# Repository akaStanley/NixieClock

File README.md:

# Nixie Tube Clock
From scratch design of a Nixie Tube Clock, with a twist. This clock sets its time using a GPS reciever, so it has the correct time anywhere around the world--and you don't have set it.

Read the "Notes on Nixie Tube Clock.rtf" for more details on the actual design. Here are some images of the design.
All the Code, PCB, and 3D model files are included here if you want to make your own. BOM cost will run you around 300$ (as of May 2025)

### The Finnished Clock

### The Clock Powered Off

### PCB Top side

### PCB Bottom side (with fix)

### Circuit Overview

### Circuit Detail
From left to right:  
12vDC to 180v boost circuit Max1771, HV shift register 1 for Hours, arduino MCU, GPS antenna, HV shift register 2 for minutes (underneath GPS)  

## 3D Printing
I bought an Ender 3 V2 and modeled a base and some trim parts for this clock.  

### "Naked" Tube legs

### Angled Base

### 3D printed ring to cover them

## Tubes!
Like any old electronics one day they will _stop working_ ... and they aren't getting any cheaper to repair.  
In 2020, the larger IN-18 tubes were 50$ each, and the smaller IN-8-2 were a measly 18$. Shipped from a wearhouse in Belarus.  
Flash forward to 2025, and the large tubes are 85$ and the small IN-8-2 are now retailing for 25$ each.

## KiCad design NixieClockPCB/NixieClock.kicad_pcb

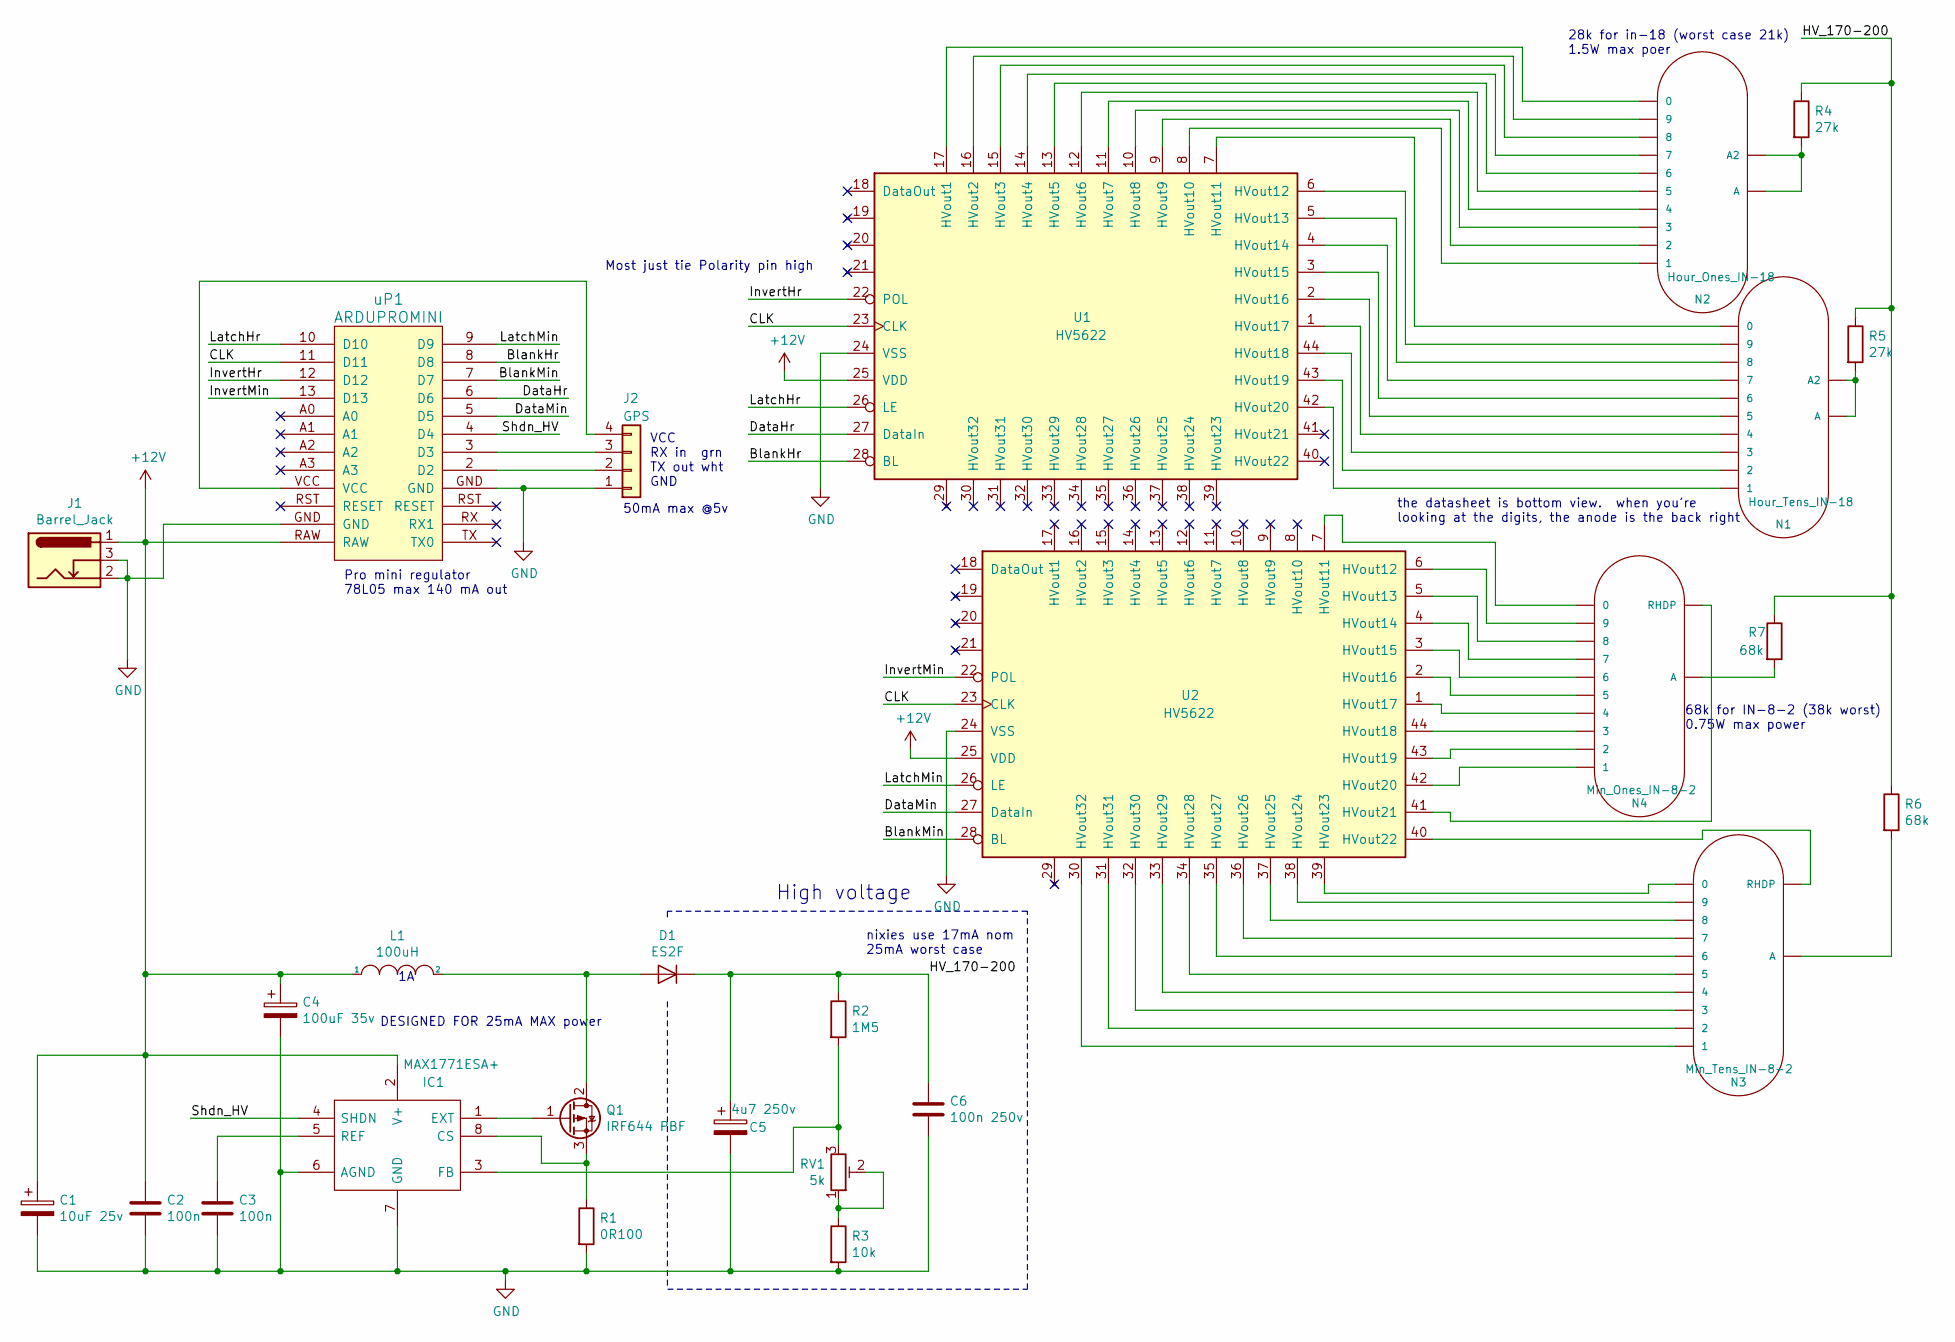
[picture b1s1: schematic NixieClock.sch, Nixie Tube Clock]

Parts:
C1: 10uF 25v; CP_Radial_Tantal_D5.5mm_P2.50mm
C2, C3: 100n; C_Disc_D5.0mm_W2.5mm_P2.50mm
C4: 100uF 35v; CP_Radial_Tantal_D9.0mm_P5.00mm
C5: 4u7 250v; CP_Radial_D8.0mm_P3.50mm
C6: 100n 250v; C_Rect_L10.3mm_W5.7mm_P7.50mm_MKS4
D1: ES2F; D_SMB
IC1: MAX1771ESA+; SOIC127P600X175-8N; Manufacturer_Part_Number MAX1771ESA+
J1: Barrel_Jack; BARREL_JACK
J2: GPS; GPS_BN180
L1: 100uH; L_Axial_L26.0mm_D9.0mm_P5.08mm_Vertical_Fastron_77A
N1: Hour_Tens_IN-18; nixies-us-IN-18-DSUB
N2: Hour_Ones_IN-18; nixies-us-IN-18-DSUB
N3: Min_Tens_IN-8-2; nixies-us-IN-8-2
N4: Min_Ones_IN-8-2; nixies-us-IN-8-2
Q1: IRF644 PBF; TO-220-3_Vertical
R1: 0R100; R_2010
R2: 1M5; R_Axial_DIN0414_L11.9mm_D4.5mm_P5.08mm_Vertical
R3: 10k; R_Axial_DIN0204_L3.6mm_D1.6mm_P1.90mm_Vertical
R4, R5: 27k; R_Axial_DIN0414_L11.9mm_D4.5mm_P5.08mm_Vertical
R6, R7: 68k; R_Axial_DIN0309_L9.0mm_D3.2mm_P2.54mm_Vertical
RV1: 5k; Potentiometer_Trimmer_Bourns_PV36W
U1, U2: HV5622; PLCC-44_THT-Socket
uP1: ARDUPROMINI; pro_mini

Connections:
+12V: C1.1, C2.1, C4.1, IC1.2 (V+), J1.1, L1.1, U1.25 (VDD), U2.25 (VDD), uP1.RAW
/BlankHr: U1.28 (BL), uP1.8 (D8)
/BlankMin: U2.28 (BL), uP1.7 (D7)
/CLK: U1.23 (CLK), U2.23 (CLK), uP1.11 (D11)
/DataHr: U1.27 (DataIn), uP1.6 (D6)
/DataMin: U2.27 (DataIn), uP1.5 (D5)
/HV_170-200: C5.1, C6.1, D1.1 (K), R2.1, R4.1, R5.1, R6.1, R7.1
/InvertHr: U1.22 (POL), uP1.12 (D12)
/InvertMin: U2.22 (POL), uP1.13 (D13)
/LatchHr: U1.26 (LE), uP1.10 (D10)
/LatchMin: U2.26 (LE), uP1.9 (D9)
/Shdn_HV: IC1.4 (SHDN), uP1.4 (D4)
GND: C1.2, C2.2, C3.2, C4.2, C5.2, C6.2, IC1.6 (AGND), IC1.7 (GND), J1.2, J1.3, J2.1, R1.2, R3.2, U1.24 (VSS), U2.24 (VSS), uP1.GND
unnamed: C3.1, IC1.5 (REF)
unnamed: D1.2 (A), L1.2, Q1.2 (D)
unnamed: IC1.1 (EXT), Q1.1 (G)
unnamed: IC1.3 (FB), R2.2, RV1.3
unnamed: IC1.8 (CS), Q1.3 (S), R1.1
unnamed: J2.2, uP1.2 (D2)
unnamed: J2.3, uP1.3 (D3)
unnamed: J2.4, uP1.VCC
unnamed: N1.0, U1.7 (HVout11)
unnamed: N1.1, U1.42 (HVout20)
unnamed: N1.2, U1.43 (HVout19)
unnamed: N1.3, U1.44 (HVout18)
unnamed: N1.4, U1.1 (HVout17)
unnamed: N1.5, U1.2 (HVout16)
unnamed: N1.6, U1.3 (HVout15)
unnamed: N1.7, U1.4 (HVout14)
unnamed: N1.8, U1.5 (HVout13)
unnamed: N1.9, U1.6 (HVout12)
unnamed: N1.A, N1.A2, R5.2
unnamed: N2.0, U1.17 (HVout1)
unnamed: N2.1, U1.8 (HVout10)
unnamed: N2.2, U1.9 (HVout9)
unnamed: N2.3, U1.10 (HVout8)
unnamed: N2.4, U1.11 (HVout7)
unnamed: N2.5, U1.12 (HVout6)
unnamed: N2.6, U1.13 (HVout5)
unnamed: N2.7, U1.14 (HVout4)
unnamed: N2.8, U1.15 (HVout3)
unnamed: N2.9, U1.16 (HVout2)
unnamed: N2.A, N2.A2, R4.2
unnamed: N3.0, U2.39 (HVout23)
unnamed: N3.1, U2.30 (HVout32)
unnamed: N3.2, U2.31 (HVout31)
unnamed: N3.3, U2.32 (HVout30)
unnamed: N3.4, U2.33 (HVout29)
unnamed: N3.5, U2.34 (HVout28)
unnamed: N3.6, U2.35 (HVout27)
unnamed: N3.7, U2.36 (HVout26)
unnamed: N3.8, U2.37 (HVout25)
unnamed: N3.9, U2.38 (HVout24)
unnamed: N3.. (RHDP), U2.40 (HVout22)
unnamed: N3.A, R6.2
unnamed: N4.0, U2.7 (HVout11)
unnamed: N4.1, U2.42 (HVout20)
unnamed: N4.2, U2.43 (HVout19)
unnamed: N4.3, U2.44 (HVout18)
unnamed: N4.4, U2.1 (HVout17)
unnamed: N4.5, U2.2 (HVout16)
unnamed: N4.6, U2.3 (HVout15)
unnamed: N4.7, U2.4 (HVout14)
unnamed: N4.8, U2.5 (HVout13)
unnamed: N4.9, U2.6 (HVout12)
unnamed: N4.. (RHDP), U2.41 (HVout21)
unnamed: N4.A, R7.2
unnamed: R3.1, RV1.1, RV1.2

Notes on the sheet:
High voltage
VCC RX in grn TX out wht GND
50mA max @5v
DESIGNED FOR 25mA MAX power
nixies use 17mA nom 25mA worst case
the datasheet is bottom view. when you're looking at the digits, the anode is the back right
28k for in-18 (worst case 21k) 1.5W max poer
Pro mini regulator 78L05 max 140 mA out
68k for IN-8-2 (38k worst) 0.75W max power
Most just tie Polarity pin high

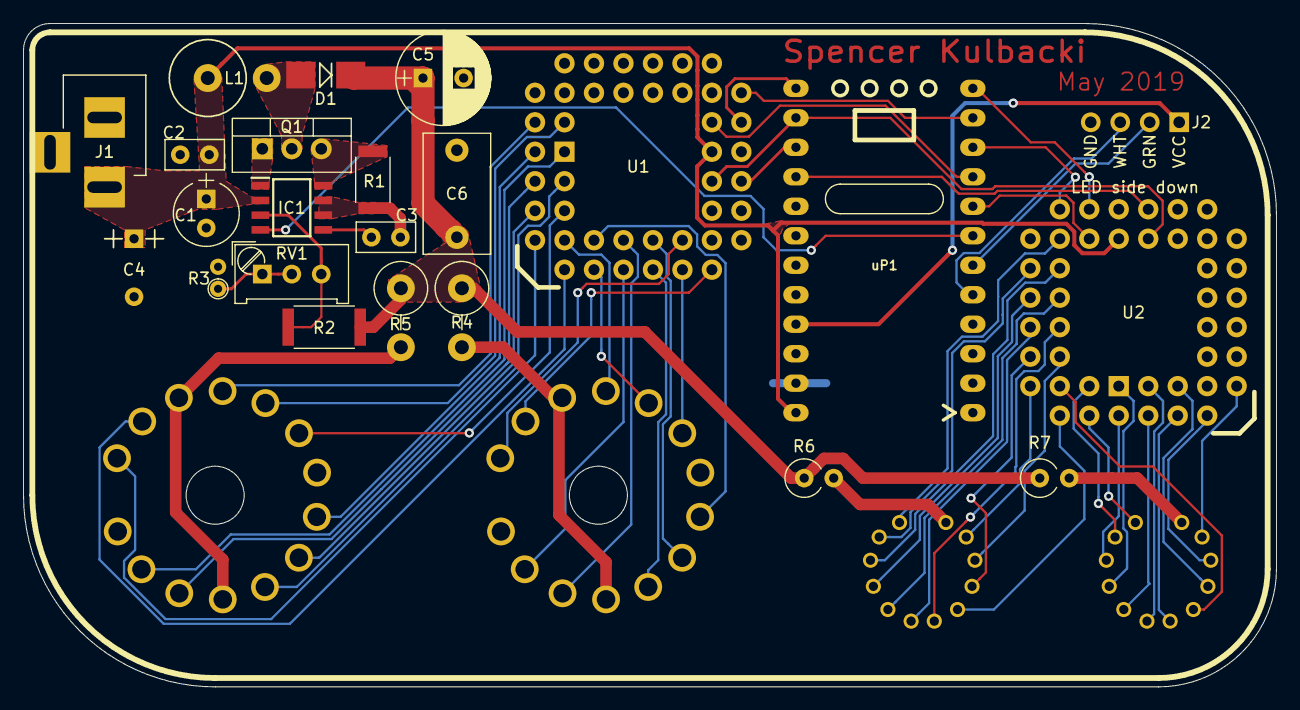
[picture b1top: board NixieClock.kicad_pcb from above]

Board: 2 copper layers, 108.0 x 57.2 mm, 27 parts (0 on the bottom side), 68 nets.

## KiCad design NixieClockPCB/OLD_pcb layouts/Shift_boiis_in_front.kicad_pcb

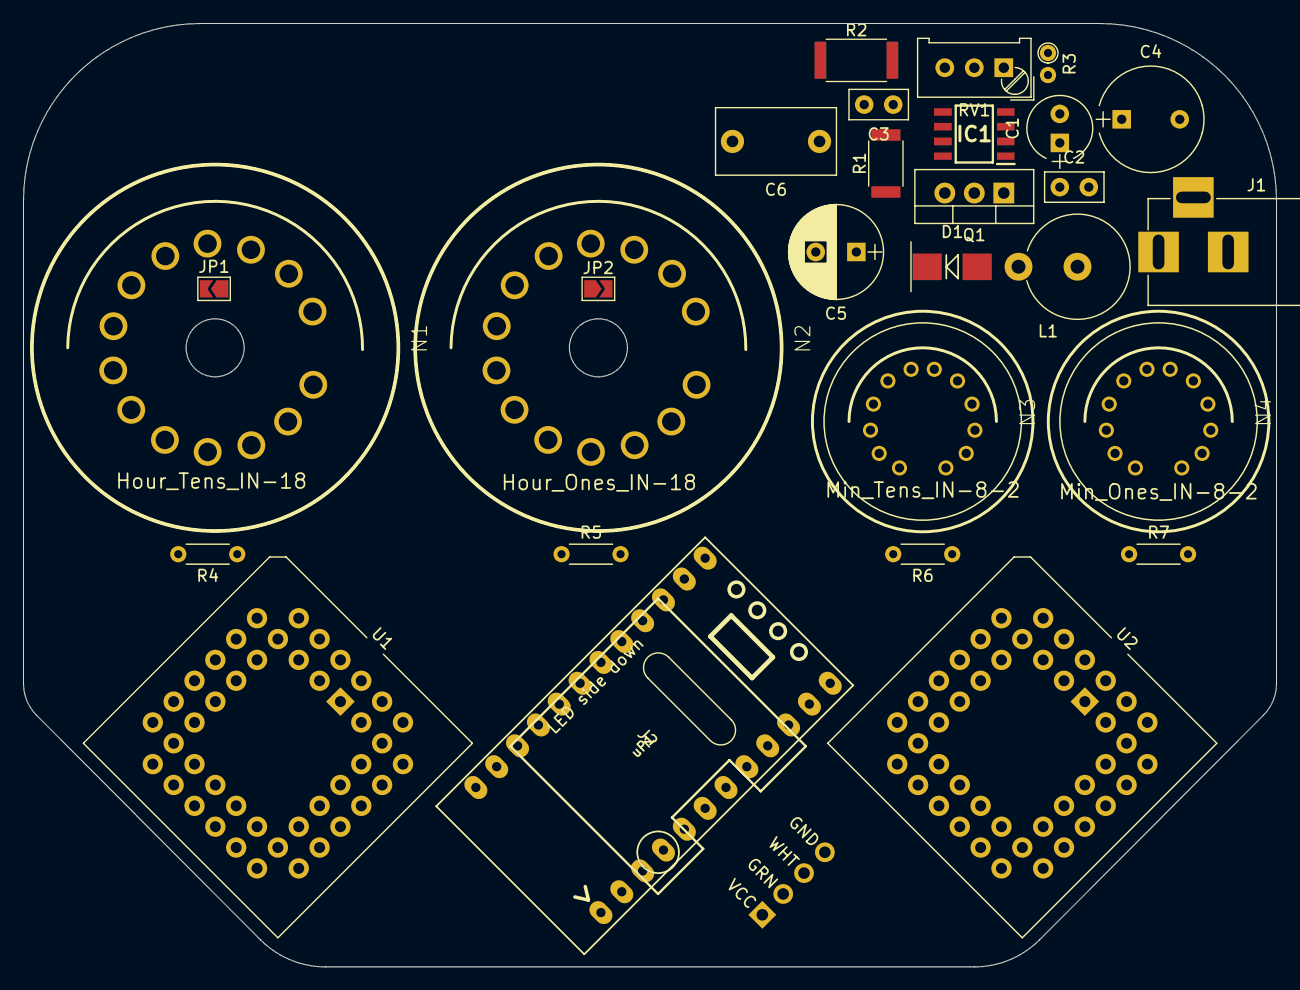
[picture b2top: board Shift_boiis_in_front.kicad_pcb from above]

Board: 2 copper layers, 108.0 x 81.3 mm, 29 parts (0 on the bottom side), 70 nets, no tracks yet.

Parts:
C1: 10uF 25v; CP_Radial_Tantal_D5.5mm_P2.50mm
C2, C3: 100n; C_Disc_D5.0mm_W2.5mm_P2.50mm
C4: 100uF 35v; CP_Radial_Tantal_D9.0mm_P5.00mm
C5: 4u7 250v; CP_Radial_D8.0mm_P3.50mm
C6: 100n 250v; C_Rect_L10.3mm_W5.7mm_P7.50mm_MKS4
D1: ES2F; D_SMB
IC1: MAX1771ESA+; SOIC127P600X175-8N
J1: Barrel_Jack; BARREL_JACK
J2: GPS; GPS_BN180
JP1, JP2: open; SolderJumper-2_P1.3mm_Open_TrianglePad1.0x1.5mm
L1: 100uH; L_Axial_L26.0mm_D9.0mm_P5.08mm_Vertical_Fastron_77A
N1: Hour_Tens_IN-18; nixies-us-IN-18-DSUB
N2: Hour_Ones_IN-18; nixies-us-IN-18-DSUB
N3: Min_Tens_IN-8-2; nixies-us-IN-8-2
N4: Min_Ones_IN-8-2; nixies-us-IN-8-2
Q1: IRF644 PBF; TO-220-3_Vertical
R1: 0R100; R_2010
R2: 1M5; R_2512
R3: 10k; R_Axial_DIN0204_L3.6mm_D1.6mm_P1.90mm_Vertical
R4, R5: 27k; R_Axial_DIN0204_L3.6mm_D1.6mm_P5.08mm_Horizontal
R6, R7: 68k; R_Axial_DIN0204_L3.6mm_D1.6mm_P5.08mm_Horizontal
RV1: 5k; Potentiometer_Trimmer_Bourns_PV36W
U1, U2: HV5622; PLCC-44_THT-Socket
uP1: ARDUPROMINI; pro_mini

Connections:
+12V: C1.1, C2.1, C4.1, IC1.2, J1.1, L1.1, U1.25, U2.25, uP1.RAW
/BlankHr: U1.28, uP1.8
/BlankMin: U2.28, uP1.9
/CLK: U1.23, U2.23, uP1.11
/DataHr: U1.27, uP1.6
/DataMin: U2.27, uP1.5
/HV_170-200: C5.1, C6.1, D1.1, R2.1, R4.1, R5.1, R6.1, R7.1
/InvertHr: U1.22, uP1.12
/InvertMin: U2.22, uP1.13
/LatchHr: U1.26, uP1.10
/LatchMin: U2.26, uP1.7
/Shdn_HV: IC1.4, uP1.4
GND: C1.2, C2.2, C3.2, C4.2, C5.2, C6.2, IC1.6, IC1.7, J1.2, J1.3, J2.1, R1.2, R3.2, U1.24, U2.24, uP1.GND
unnamed: C3.1, IC1.5
unnamed: D1.2, L1.2, Q1.2
unnamed: IC1.1, Q1.1
unnamed: IC1.3, R2.2, RV1.3
unnamed: IC1.8, Q1.3, R1.1
unnamed: J2.2, uP1.2
unnamed: J2.3, uP1.3
unnamed: J2.4, uP1.VCC
unnamed: JP1.1, N1.A2
unnamed: JP1.2, N1.A, R4.2
unnamed: JP2.1, N2.A, R5.2
unnamed: JP2.2, N2.A2
unnamed: N1.0, U1.8
unnamed: N1.1, U1.17
unnamed: N1.2, U1.16
unnamed: N1.3, U1.15
unnamed: N1.4, U1.14
unnamed: N1.5, U1.13
unnamed: N1.6, U1.12
unnamed: N1.7, U1.11
unnamed: N1.8, U1.10
unnamed: N1.9, U1.9
unnamed: N2.0, U1.42
unnamed: N2.1, U1.7
unnamed: N2.2, U1.6
unnamed: N2.3, U1.5
unnamed: N2.4, U1.4
unnamed: N2.5, U1.3
unnamed: N2.6, U1.2
unnamed: N2.7, U1.1
unnamed: N2.8, U1.44
unnamed: N2.9, U1.43
unnamed: N3.0, U2.8
unnamed: N3.1, U2.17
unnamed: N3.2, U2.16
unnamed: N3.3, U2.15
unnamed: N3.4, U2.14
unnamed: N3.5, U2.13
unnamed: N3.6, U2.12
unnamed: N3.7, U2.11
unnamed: N3.8, U2.10
unnamed: N3.9, U2.9
unnamed: N3.., U2.40
unnamed: N3.A, R6.2
unnamed: N4.0, U2.42
unnamed: N4.1, U2.7
unnamed: N4.2, U2.6
unnamed: N4.3, U2.5
unnamed: N4.4, U2.4
unnamed: N4.5, U2.3
unnamed: N4.6, U2.2
unnamed: N4.7, U2.1
unnamed: N4.8, U2.44
unnamed: N4.9, U2.43
unnamed: N4.., U2.41
unnamed: N4.A, R7.2
unnamed: R3.1, RV1.1, RV1.2

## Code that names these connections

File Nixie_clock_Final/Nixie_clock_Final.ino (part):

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int dstOffsetMinutes = 0; //Daylight Time offset

const int clkPin = 11;   // OC2A output pin is 11 do not change
const int dataMin = 5;
const int dataHr = 6;

const int latchMin = 9;
const int latchHr = 10;

uint8_t prevMin = -1;
uint8_t currentMin = 0; //Shown time minute stored here
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
  pinMode(clkPin, OUTPUT);
  digitalWrite(clkPin, LOW);
  pinMode(dataHr, OUTPUT);
  digitalWrite(dataHr, LOW);
  pinMode(dataMin, OUTPUT);
  digitalWrite(dataMin, LOW);
  pinMode(latchMin, OUTPUT);
  digitalWrite(latchMin, LOW);
  pinMode(latchHr, OUTPUT);
  digitalWrite(latchHr, LOW);

  shiftOutData(dataMin, clkPin, latchMin, minuteData); //Send 0 to clear registers
  shiftOutData(dataHr, clkPin, latchHr, hourData); //Send 0 to clear registers

  delay(500); //wait 1/2 second for power to stabalize
  randomSeed(analogRead(A0)); //Read from floating A0 pin to seed Random number gen
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        prevMin = currentMin;
        timeToBitMinute(currentMin); //convert time from integer to binary
        timeToBitHour(currentHr);
        shiftOutData(dataMin, clkPin, latchMin, minuteData); //send to tubes via shift register
        shiftOutData(dataHr, clkPin, latchHr, hourData);

        //Debugging:
        //Serial.print("\nTimeDisplayed");
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      //Serial.println(i);
      timeToBitMinute(i);
      timeToBitHour(i);
      shiftOutData(dataMin, clkPin, latchMin, minuteData);
      shiftOutData(dataHr, clkPin, latchHr, hourData);
      delay(750);
    }
    for (int i = 88; i >= 0; i -= 11) { // Decrement down by 11
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      //Serial.println(i);
      timeToBitMinute(i);
      timeToBitHour(i);
      shiftOutData(dataMin, clkPin, latchMin, minuteData);
      shiftOutData(dataHr, clkPin, latchHr, hourData);
      delay(750);
    }
    TubeCleaning = false; // End the tube cleaning after loop completes
    timeToBitMinute(2); //set the clock back to the correct time
    timeToBitHour(12);
    shiftOutData(dataMin, clkPin, latchMin, minuteData); //send to tubes via shift register
    shiftOutData(dataHr, clkPin, latchHr, hourData);
  }

  if (currentHr == 12 && currentMin == 10) {
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    randHr = random(0, 99);
    timeToBitMinute(randMin); //show random number on minutes
    timeToBitHour(randHr); //show random number on hour
    shiftOutData(dataMin, clkPin, latchMin, minuteData);
    shiftOutData(dataHr, clkPin, latchHr, hourData);
    delay(100);
  }
}//end random pattern display function
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
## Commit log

2023-05-05 Commit all files
    Adding notes in readme and clean up some leftover project files
2023-05-05 Added info
2023-05-05 markdown is annoying
2023-05-05 File cleanup
    Update BOM
2025-05-05 Update SW libraries & code for 2025
2025-05-05 Update cleaning sequence, improve accuracy
